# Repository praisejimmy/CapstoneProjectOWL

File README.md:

# CapstoneProjectOWL
CPE capstone repository for Project OWL

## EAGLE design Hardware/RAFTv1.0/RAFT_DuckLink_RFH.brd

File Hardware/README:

Capstone Project RAFT Hardware
***
Ryan Myers
Tristan Chutka
Jake Loveland
Noah Palumbo
***

This folder contains all hardware design files for the RAFT system.
Autodesk EAGLE is used for circuit and PCB design.

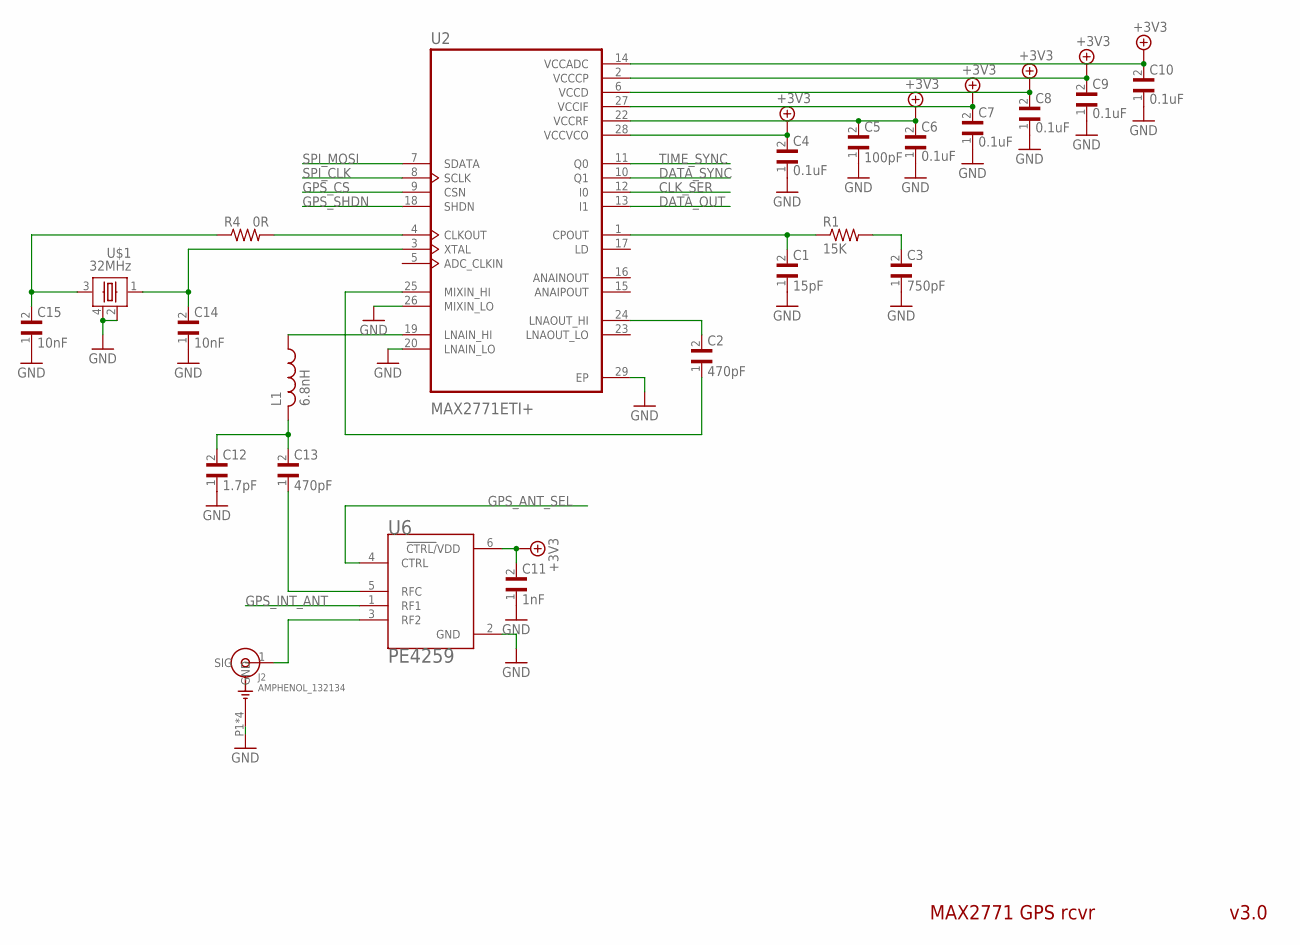
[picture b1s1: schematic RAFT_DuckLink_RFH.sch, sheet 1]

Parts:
C1: 15pF; CAPC1005X55N
C2, C13: 470pF; CAPC1005X55N
C3: 750pF; CAPC1608X90N
C4, C6, C7, C8, C9, C10: 0.1uF; CAPC1005X55N
C5: 100pF; CAPC1005X55N
C11: 1nF; CAPC1005X55N
C12: 1.7pF; CAPC1005X55N
C14, C15: 10nF; CAPC1005X55N
J2: AMPHENOL_132134; AMPHENOL_132134-15
L1: 6.8nH; INDC1005X55N
R1: 15K; RESC1005X40N
R4: 0R; RESC1005X40N
U2: MAX2771ETI+; QFN50P500X500X80-29N
U6: PE4259; SOT65P215X110-6N
U$1: 32MHz; SMD-4

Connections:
+3.3V: C4.2, C5.2, C6.2, C7.2, C8.2, C9.2, C10.2, C11.2, U2.2 (VCCCP), U2.6 (VCCD), U2.14 (VCCADC), U2.22 (VCCRF), U2.27 (VCCIF), U2.28 (VCCVCO), U6.6 (!CTRL/!VDD); also elsewhere on the board
CLK_SER: U2.12 (I0); also elsewhere on the board
DATA_OUT: U2.13 (I1); also elsewhere on the board
DATA_SYNC: U2.10 (Q1); also elsewhere on the board
GND: C1.1, C3.1, C4.1, C5.1, C6.1, C7.1, C8.1, C9.1, C10.1, C11.1, C12.1, C14.1, C15.1, J2.P1 (GND), J2.P2 (GND), J2.P3 (GND), J2.P4 (GND), U2.20 (LNAIN_LO), U2.26 (MIXIN_LO), U2.29 (EP), U6.2 (GND), U$1.2, U$1.4; also elsewhere on the board
GPS_ANT_SEL: U6.4 (CTRL); also elsewhere on the board
GPS_CS: U2.9 (CSN); also elsewhere on the board
GPS_INT_ANT: U6.1 (RF1); also elsewhere on the board
GPS_SHDN: U2.18 (SHDN); also elsewhere on the board
unnamed: C1.2, R1.1, U2.1 (CPOUT)
unnamed: C3.2, R1.2
unnamed: C2.2, U2.24 (LNAOUT_HI)
unnamed: C2.1, U2.25 (MIXIN_HI)
unnamed: L1.1, U2.19 (LNAIN_HI)
unnamed: C13.1, U6.5 (RFC)
unnamed: J2.1 (SIG), U6.3 (RF2)
unnamed: C12.2, C13.2, L1.2
unnamed: C15.2, R4.1, U$1.3
unnamed: C14.2, U2.3 (XTAL), U$1.1
unnamed: R4.2, U2.4 (CLKOUT)
SPI_CLK: U2.8 (SCLK); also elsewhere on the board
SPI_MOSI: U2.7 (SDATA); also elsewhere on the board
TIME_SYNC: U2.11 (Q0); also elsewhere on the board

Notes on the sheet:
MAX2771 GPS rcvr
v3.0

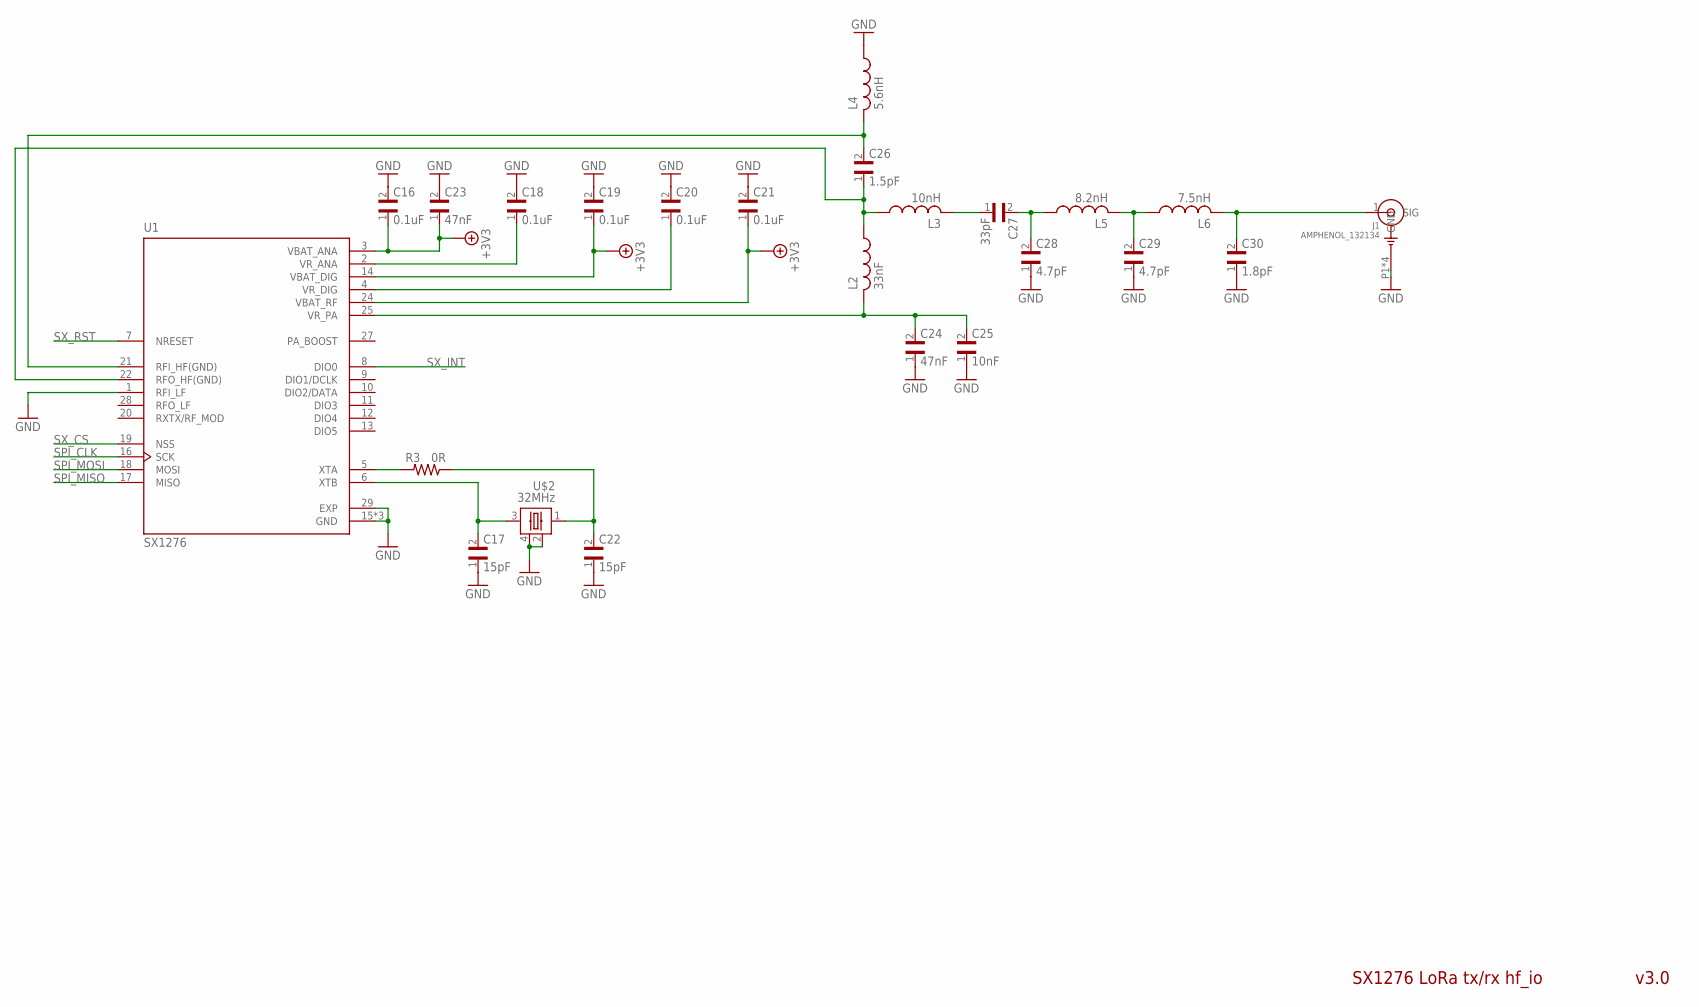
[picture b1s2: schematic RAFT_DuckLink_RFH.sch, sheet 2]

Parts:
C16, C18, C19, C20, C21: 0.1uF; CAPC1005X55N
C17, C22: 15pF; CAPC1005X55N
C23, C24: 47nF; CAPC1005X55N
C25: 10nF; CAPC1005X55N
C26: 1.5pF; CAPC1005X55N
C27: 33pF; CAPC1005X55N
C28, C29: 4.7pF; CAPC1005X55N
C30: 1.8pF; CAPC1005X55N
J1: AMPHENOL_132134; AMPHENOL_132134-15
L2: 33nF; INDC1005X55N
L3: 10nH; INDC1005X55N
L4: 5.6nH; INDC1005X55N
L5: 8.2nH; INDC1005X55N
L6: 7.5nH; INDC1005X55N
R3: 0R; RESC1005X40N
U1: SX1276; QFN65P600X600X100-29N
U$2: 32MHz; SMD-4

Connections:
+3.3V: C16.1, C19.1, C21.1, C23.1, U1.3 (VBAT_ANA), U1.14 (VBAT_DIG), U1.24 (VBAT_RF); also elsewhere on the board
GND: C16.2, C17.1, C18.2, C19.2, C20.2, C21.2, C22.1, C23.2, C24.1, C25.1, C28.1, C29.1, C30.1, J1.P1 (GND), J1.P2 (GND), J1.P3 (GND), J1.P4 (GND), L4.1, U1.1 (RFI_LF), U1.15 (GND), U1.23 (GND), U1.26 (GND), U1.29 (EXP), U$2.2, U$2.4; also elsewhere on the board
unnamed: C24.2, C25.2, L2.2, U1.25 (VR_PA)
unnamed: C18.1, U1.2 (VR_ANA)
unnamed: C22.2, R3.1, U$2.1
unnamed: C20.1, U1.4 (VR_DIG)
unnamed: C17.2, U1.6 (XTB), U$2.3
unnamed: C26.1, L2.1, L3.1, U1.22 (RFO_HF(GND))
unnamed: C26.2, L4.2, U1.21 (RFI_HF(GND))
unnamed: C27.1, L3.2
unnamed: C27.2, C28.2, L5.1
unnamed: C29.2, L5.2, L6.1
unnamed: C30.2, J1.1 (SIG), L6.2
unnamed: R3.2, U1.5 (XTA)
SPI_CLK: U1.16 (SCK); also elsewhere on the board
SPI_MISO: U1.17 (MISO); also elsewhere on the board
SPI_MOSI: U1.18 (MOSI); also elsewhere on the board
SX_CS: U1.19 (NSS); also elsewhere on the board
SX_INT: U1.8 (DIO0); also elsewhere on the board
SX_RST: U1.7 (NRESET); also elsewhere on the board

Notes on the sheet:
SX1276 LoRa tx/rx hf_io
v3.0

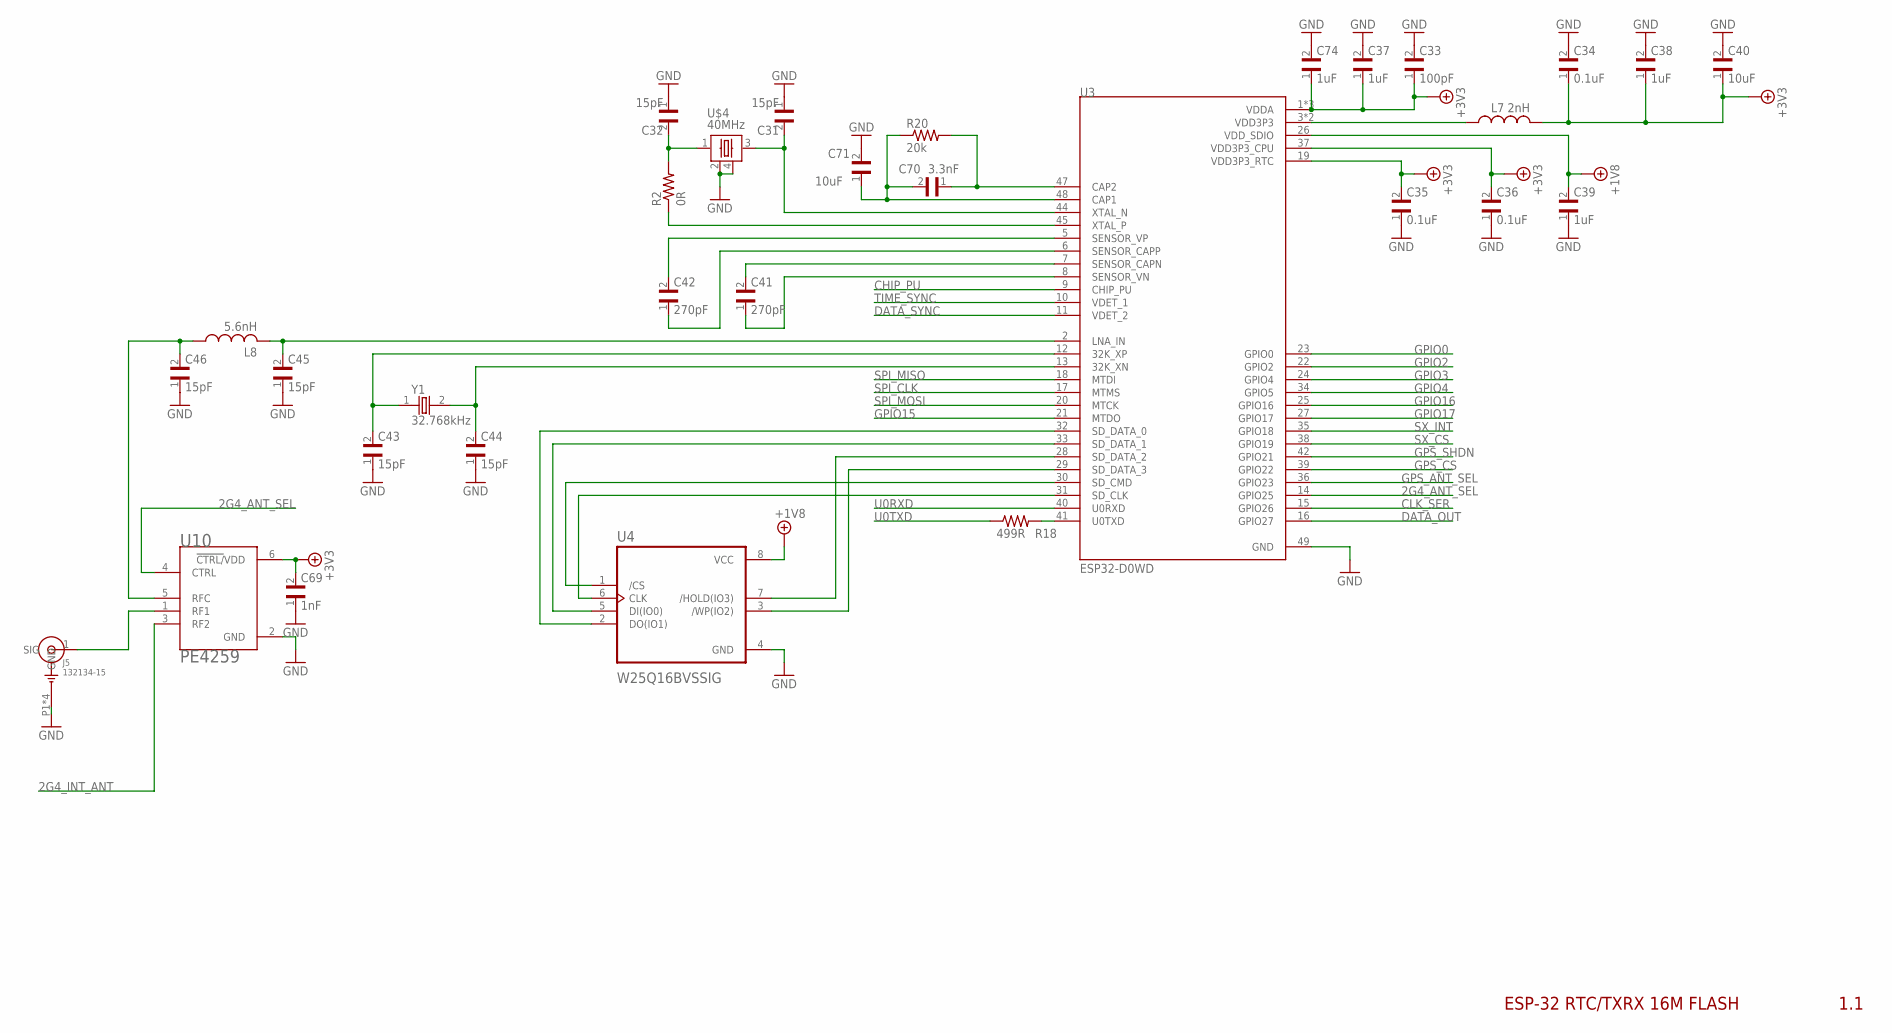
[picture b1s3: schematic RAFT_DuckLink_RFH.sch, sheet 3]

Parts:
C31, C32, C43, C44, C45, C46: 15pF; CAPC1005X55N
C33: 100pF; CAPC1005X55N
C34, C35, C36: 0.1uF; CAPC1005X55N
C37, C38, C39, C74: 1uF; CAPC1005X70N
C40, C71: 10uF; CAPC1005X70N
C41, C42: 270pF; CAPC1005X55N
C69: 1nF; CAPC1005X55N
C70: 3.3nF; CAPC1005X55N
J5: 132134-15; AMPHENOL_132134-15
L7: 2nH; INDC1005X55N
L8: 5.6nH; INDC1005X55N
R2: 0R; RESC1005X40N
R18: 499R; RESC1005X35N
R20: 20k; RESC1005X35N
U3: ESP32-D0WD; QFN35P500X500X90-49N
U4: W25Q16BVSSIG; SOIC127P790X216-8N
U10: PE4259; SOT65P215X110-6N
U$4: 40MHz; SMD-4
Y1: 32.768kHz; OSCCC150X320X80-2N

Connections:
2G4_ANT_SEL: U3.14 (GPIO25), U10.4 (CTRL)
2G4_INT_ANT: U10.3 (RF2); also elsewhere on the board
+1.8V: C39.2, U3.26 (VDD_SDIO), U4.8 (VCC)
+3.3V: C33.1, C34.1, C35.2, C36.2, C37.1, C38.1, C40.1, C69.2, C74.1, L7.2, U3.1 (VDDA), U3.19 (VDD3P3_RTC), U3.37 (VDD3P3_CPU), U3.43 (VDDA), U3.46 (VDDA), U10.6 (!CTRL/!VDD); also elsewhere on the board
CHIP_PU: U3.9 (CHIP_PU); also elsewhere on the board
CLK_SER: U3.15 (GPIO26); also elsewhere on the board
DATA_OUT: U3.16 (GPIO27); also elsewhere on the board
DATA_SYNC: U3.11 (VDET_2); also elsewhere on the board
GND: C31.1, C32.1, C33.2, C34.2, C35.1, C36.1, C37.2, C38.2, C39.1, C40.2, C43.1, C44.1, C45.1, C46.1, C69.1, C71.2, C74.2, J5.P1 (GND), J5.P2 (GND), J5.P3 (GND), J5.P4 (GND), U3.49 (GND), U4.4 (GND), U10.2 (GND), U$4.2, U$4.4; also elsewhere on the board
GPIO0: U3.23 (GPIO0); also elsewhere on the board
GPIO2: U3.22 (GPIO2); also elsewhere on the board
GPIO3: U3.24 (GPIO4); also elsewhere on the board
GPIO4: U3.34 (GPIO5); also elsewhere on the board
GPIO15: U3.21 (MTDO); also elsewhere on the board
GPIO16: U3.25 (GPIO16); also elsewhere on the board
GPIO17: U3.27 (GPIO17); also elsewhere on the board
GPS_ANT_SEL: U3.36 (GPIO23); also elsewhere on the board
GPS_CS: U3.39 (GPIO22); also elsewhere on the board
GPS_SHDN: U3.42 (GPIO21); also elsewhere on the board
unnamed: R2.1, U3.45 (XTAL_P)
unnamed: C31.2, U3.44 (XTAL_N), U$4.3
unnamed: L7.1, U3.3 (VDD3P3), U3.4 (VDD3P3)
unnamed: C41.1, U3.8 (SENSOR_VN)
unnamed: C41.2, U3.7 (SENSOR_CAPN)
unnamed: C42.1, U3.6 (SENSOR_CAPP)
unnamed: C42.2, U3.5 (SENSOR_VP)
unnamed: C32.2, R2.2, U$4.1
unnamed: R18.2, U3.41 (U0TXD)
unnamed: U3.30 (SD_CMD), U4.1 (/CS)
unnamed: U3.31 (SD_CLK), U4.6 (CLK)
unnamed: U3.28 (SD_DATA_2), U4.7 (/HOLD(IO3))
unnamed: U3.29 (SD_DATA_3), U4.3 (/WP(IO2))
unnamed: U3.33 (SD_DATA_1), U4.5 (DI(IO0))
unnamed: U3.32 (SD_DATA_0), U4.2 (DO(IO1))
unnamed: C43.2, U3.12 (32K_XP), Y1.1
unnamed: C46.2, L8.1, U10.5 (RFC)
unnamed: C44.2, U3.13 (32K_XN), Y1.2
unnamed: C45.2, L8.2, U3.2 (LNA_IN)
unnamed: J5.1 (SIG), U10.1 (RF1)
unnamed: C70.1, R20.2, U3.47 (CAP2)
unnamed: C70.2, C71.1, R20.1, U3.48 (CAP1)
SPI_CLK: U3.17 (MTMS); also elsewhere on the board
SPI_MISO: U3.18 (MTDI); also elsewhere on the board
SPI_MOSI: U3.20 (MTCK); also elsewhere on the board
SX_CS: U3.38 (GPIO19); also elsewhere on the board
SX_INT: U3.35 (GPIO18); also elsewhere on the board
TIME_SYNC: U3.10 (VDET_1); also elsewhere on the board
U0RXD: U3.40 (U0RXD); also elsewhere on the board
U0TXD: R18.1; also elsewhere on the board

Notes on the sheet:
1.1
ESP-32 RTC/TXRX 16M FLASH

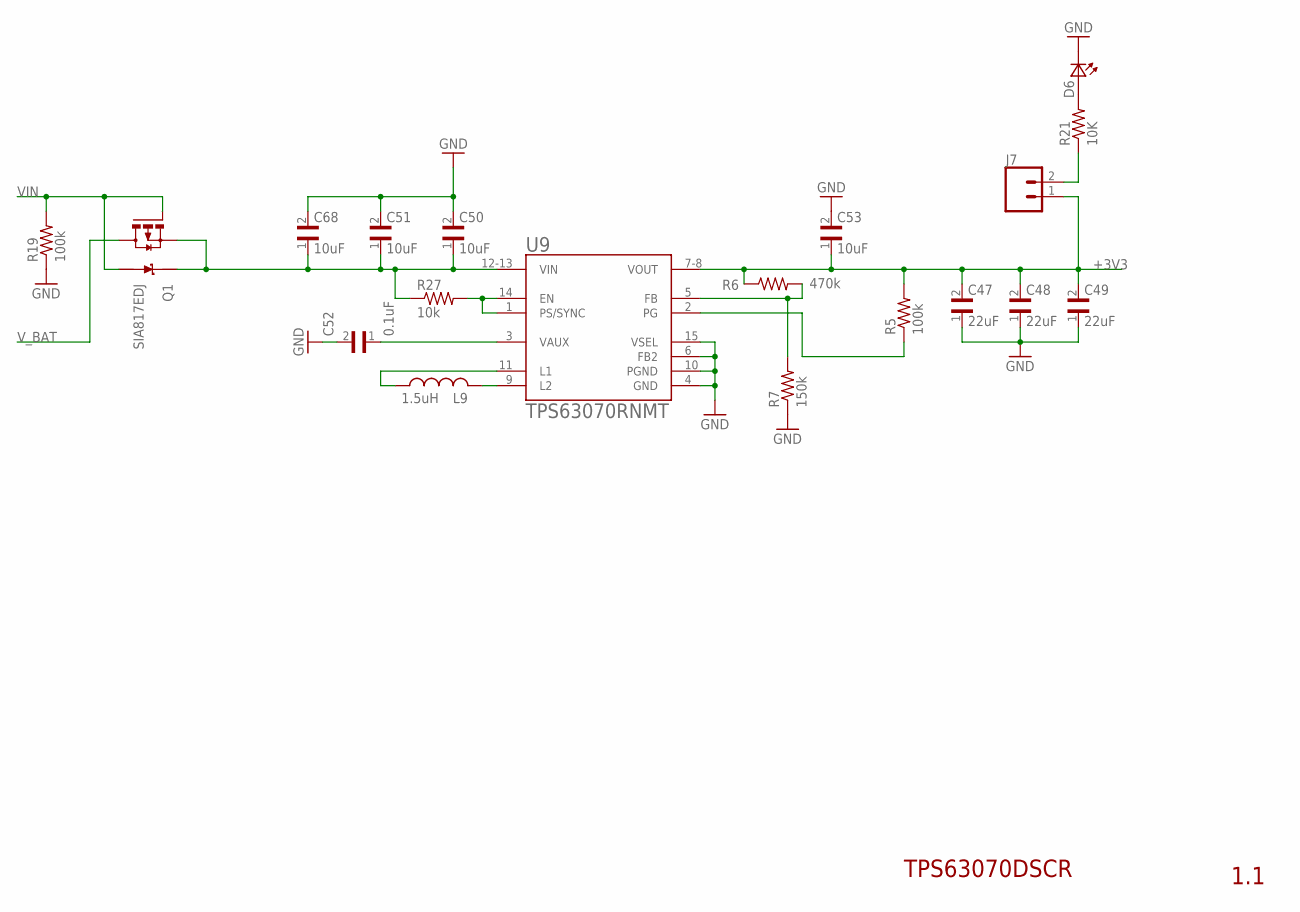
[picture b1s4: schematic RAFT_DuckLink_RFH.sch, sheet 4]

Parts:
C47, C48, C49: 22uF; CAPC1608X100N
C50, C51, C53, C68: 10uF; CAPC1005X70N
C52: 0.1uF; CAPC1005X55N
D6: LTST-C190GKT; 0603
J7: CONN_02; 1X02
L9: 1.5uH; INDC1608X95N
Q1: SIA817EDJ; POWERPAKSC-70
R5, R19: 100k; RESC1005X40N
R6: 470k; RESC1005X35N
R7: 150k; RESC1005X35N
R21: 10K; RESC1005X40N
R27: 10k; RESC1005X40N
U9: TPS63070RNMT; QFN50P250X300X100-15N

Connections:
+3V3: C47.2, C48.2, C49.2, C53.1, J7.1, R5.2, R6.1, U9.7-8 (VOUT)
GND: C47.1, C48.1, C49.1, C50.2, C51.2, C52.2, C53.2, C68.2, D6.1 (K2), R7.1, R19.1, U9.4 (GND), U9.6 (FB2), U9.10 (PGND), U9.15 (VSEL); also elsewhere on the board
unnamed: C52.1, U9.3 (VAUX)
unnamed: L9.1, U9.11 (L1)
unnamed: L9.2, U9.9 (L2)
unnamed: R5.1, U9.2 (PG)
unnamed: R6.2, R7.2, U9.5 (FB)
unnamed: D6.2 (A2), R21.2
unnamed: R27.2, U9.1 (PS/SYNC), U9.14 (EN)
unnamed: J7.2, R21.1
VIN: Q1.1 (A), Q1.5 (G), R19.2; also elsewhere on the board
VIN_SYS: C50.1, C51.1, C68.1, Q1.4 (S), Q1.6 (K), R27.1, U9.12-13 (VIN)
V_BAT: Q1.3 (D); also elsewhere on the board

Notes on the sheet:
TPS63070DSCR
1.1

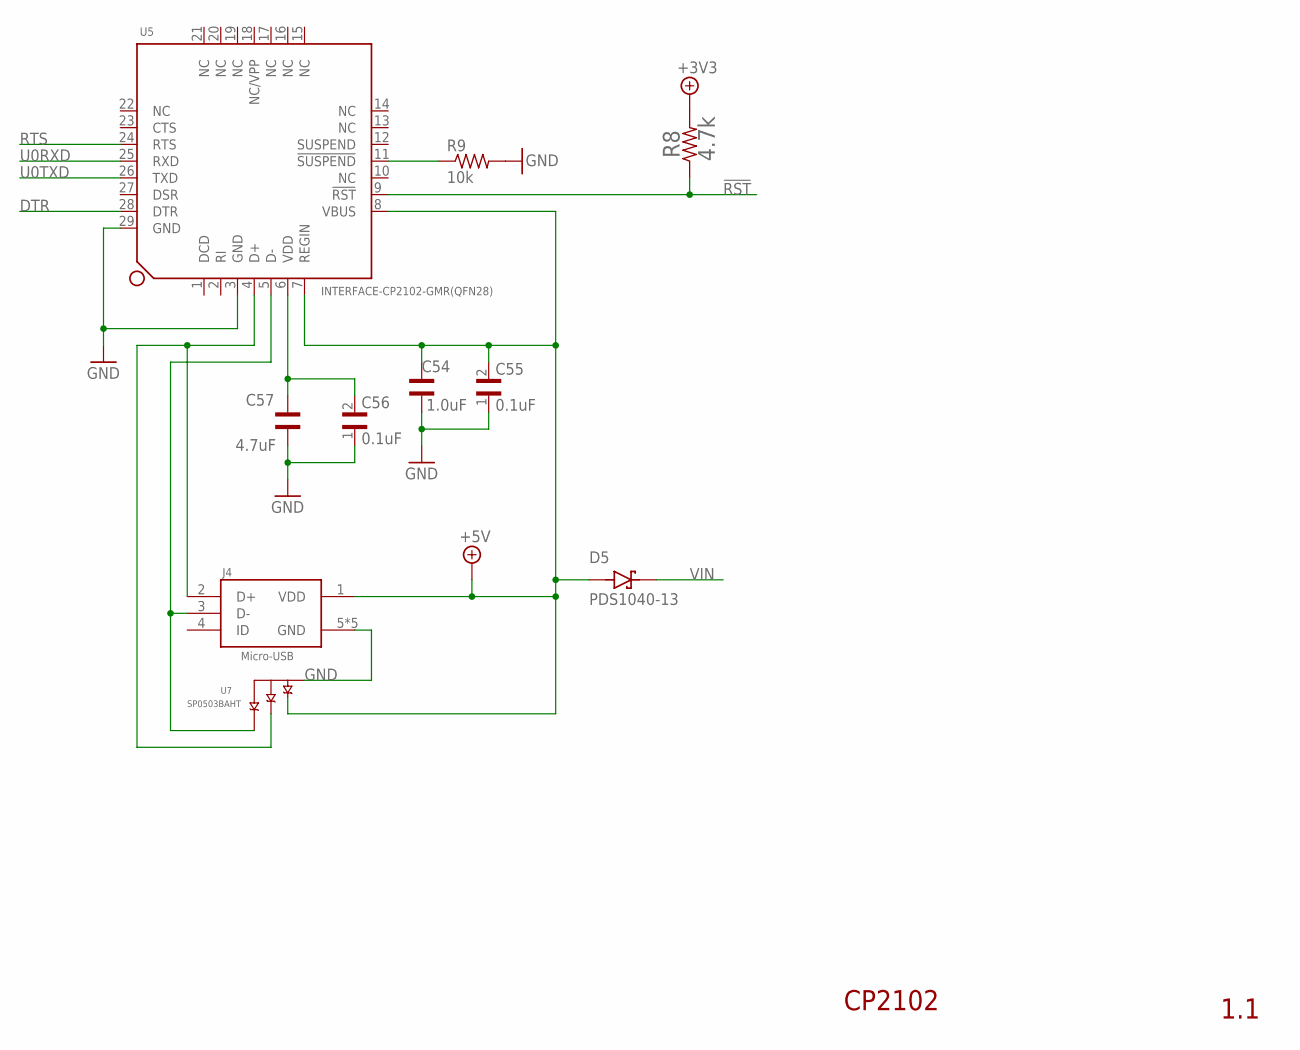
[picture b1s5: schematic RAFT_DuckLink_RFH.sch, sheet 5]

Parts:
C54: 1.0uF; CAPC1005X70N
C55, C56: 0.1uF; CAPC1005X55N
C57: 4.7uF; CAPC1005X55N
D5: PDS1040-13; DIO_PDS1040-13
J4: Micro-USB; MOLEX_105017-0001
R8: 4.7k; RESC1005X35N
R9: 10k; RESC1005X40N
U5: INTERFACE-CP2102-GMR(QFN28); QFN28G_0.5-5X5MM
U7: SP0503BAHT; SOT143

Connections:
!RST: R8.1, U5.9 (!RST)
+3.3V: R8.2; also elsewhere on the board
+5V: C54.2, C55.2, D5.1 (A), D5.2 (A), J4.1 (VDD), U5.7 (REGIN), U5.8 (VBUS), U7.2 (A); also elsewhere on the board
DTR: U5.28 (DTR); also elsewhere on the board
GND: C54.1, C55.1, C56.1, C57.1, J4.5 (GND), J4.P$1 (GND), J4.P$2 (GND), J4.P$8 (GND), J4.P$9 (GND), R9.2, U5.3 (GND), U5.29 (GND), U7.1 (GND); also elsewhere on the board
unnamed: R9.1, U5.11 (!SUSPEND)
unnamed: C56.2, C57.2, U5.6 (VDD)
unnamed: J4.3 (D-), U5.5 (D-), U7.4 (C)
unnamed: J4.2 (D+), U5.4 (D+), U7.3 (B)
RTS: U5.24 (RTS); also elsewhere on the board
U0RXD: U5.25 (RXD); also elsewhere on the board
U0TXD: U5.26 (TXD); also elsewhere on the board
VIN: D5.3 (K); also elsewhere on the board

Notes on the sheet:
CP2102
1.1

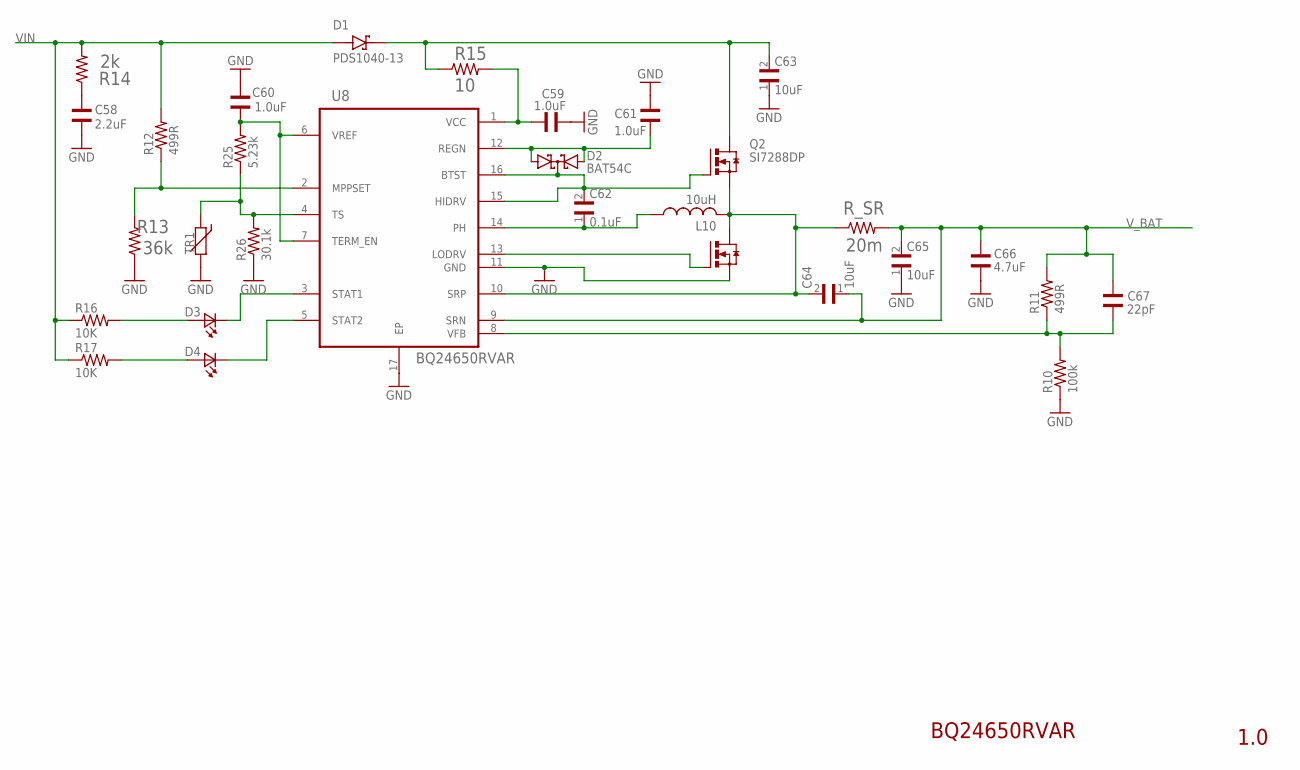
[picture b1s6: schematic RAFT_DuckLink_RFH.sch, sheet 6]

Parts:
C58: 2.2uF; CAPC1005X55N
C59, C60, C61: 1.0uF; CAPC1005X70N
C62: 0.1uF; CAPC1005X55N
C63, C64, C65: 10uF; CAPC1005X70N
C66: 4.7uF; CAPC1005X55N
C67: 22pF; CAPC1005X55N
D1: PDS1040-13; DIO_PDS1040-13
D2: BAT54C; SOT23
D3, D4: LTST-C190GKT; 0603
L10: 10uH; INDC1608X90N
Q2: SI7288DP; POWERPAK-SO8_1
R10: 100k; RESC1005X40N
R11, R12: 499R; RESC1005X35N
R13: 36k; RESC1005X40N
R14: 2k; RESC1005X40N
R15: 10; RESC1005X35N
R16, R17: 10K; RESC1005X40N
R25: 5.23k; RESC1005X40N
R26: 30.1k; RESC1005X40N
R_SR: 20m; RESC1608X55N
TR1: THERMISTOR_R-2,5; RS-2,5
U8: BQ24650RVAR; QFN50P350X350X100-17N

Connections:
GND: C58.1, C59.2, C60.2, C61.2, C63.1, C65.1, C66.1, Q2.3 (S1), R10.1, R13.1, R26.1, TR1.2, U8.11 (GND), U8.17 (EP); also elsewhere on the board
unnamed: Q2.4 (G1), U8.13 (LODRV)
unnamed: C60.1, R25.2, U8.6 (VREF), U8.7 (TERM_EN)
unnamed: R12.1, R13.2, U8.2 (MPPSET)
unnamed: C59.1, R15.2, U8.1 (VCC)
unnamed: C61.1, D2.1 (A1), D2.2 (A2), U8.12 (REGN)
unnamed: C62.2, D2.3 (CC), Q2.2 (G), U8.15 (HIDRV), U8.16 (BTST)
unnamed: C67.1, R10.2, R11.1, U8.8 (VFB)
unnamed: C64.2, L10.2, Q2.1 (S), Q2.5 (D1), Q2.6 (D1), R_SR.1, U8.10 (SRP)
unnamed: D4.2 (A2), R17.2
unnamed: D3.2 (A2), R16.2
unnamed: D4.1 (K2), U8.5 (STAT2)
unnamed: D3.1 (K2), U8.3 (STAT1)
unnamed: C62.1, L10.1, U8.14 (PH)
unnamed: C58.2, R14.1
PACK_THERM: R25.1, R26.2, TR1.1, U8.4 (TS)
SC_VIN: C63.2, D1.3 (K), Q2.7 (D), Q2.8 (D), R15.1
VIN: D1.1 (A), D1.2 (A), R12.2, R14.2, R16.1, R17.1; also elsewhere on the board
V_BAT: C64.1, C65.2, C66.2, C67.2, R11.2, R_SR.2, U8.9 (SRN); also elsewhere on the board

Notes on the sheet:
BQ24650RVAR
1.0

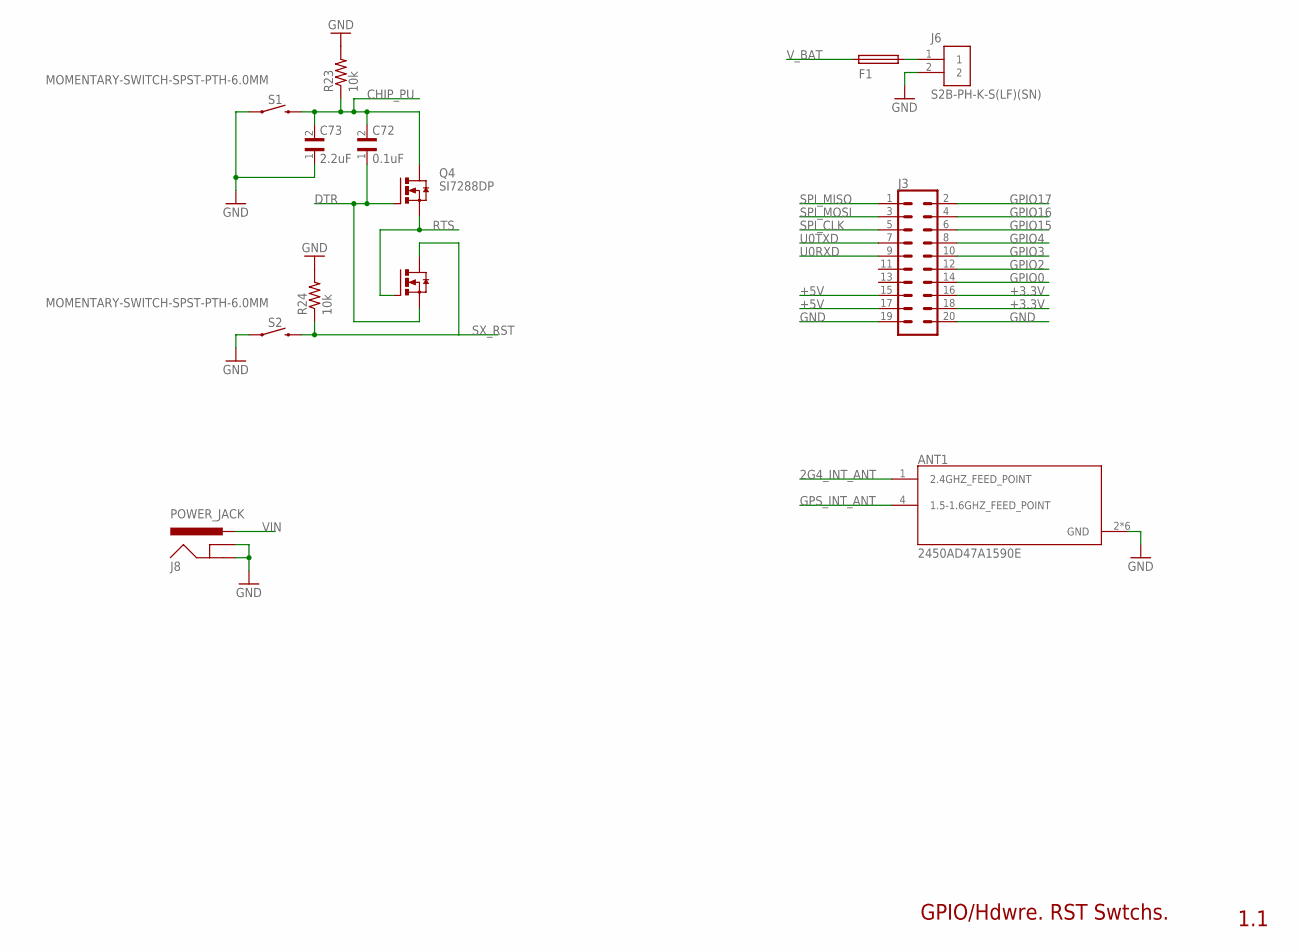
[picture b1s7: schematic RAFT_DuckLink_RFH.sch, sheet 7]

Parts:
ANT1: 2450AD47A1590E; ANT_2450AD47A1590E
C72: 0.1uF; CAPC1005X55N
C73: 2.2uF; CAPC1005X55N
F1: LITTLEFUSE
J3: CONN_10X2; 2X10
J6: S2B-PH-K-S(LF)(SN); JST_S2B-PH-K-S(LF)(SN)
J8: POWER_JACK; POWER_JACK_PTH
Q4: SI7288DP; POWERPAK-SO8_1
R23, R24: 10k; RESC1005X40N
S1, S2: MOMENTARY-SWITCH-SPST-PTH-6.0MM; TACTILE_SWITCH_PTH_6.0MM

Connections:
2G4_INT_ANT: ANT1.1 (2.4GHZ_FEED_POINT); also elsewhere on the board
+3.3V: J3.16, J3.18; also elsewhere on the board
+5V: J3.15, J3.17; also elsewhere on the board
CHIP_PU: C72.2, C73.2, Q4.7 (D), Q4.8 (D), R23.1, S1.3 (2); also elsewhere on the board
DTR: C72.1, Q4.2 (G), Q4.3 (S1); also elsewhere on the board
GND: ANT1.2 (GND), ANT1.3 (GND), ANT1.5 (GND), ANT1.6 (GND), ANT1.7 (GND), ANT1.8 (GND), C73.1, J3.19, J3.20, J6.2, J8.GND, J8.GNDBREAK, R23.2, R24.2, S1.1, S2.1; also elsewhere on the board
GPIO0: J3.14; also elsewhere on the board
GPIO2: J3.12; also elsewhere on the board
GPIO3: J3.10; also elsewhere on the board
GPIO4: J3.8; also elsewhere on the board
GPIO15: J3.6; also elsewhere on the board
GPIO16: J3.4; also elsewhere on the board
GPIO17: J3.2; also elsewhere on the board
GPS_INT_ANT: ANT1.4 (1.5-1.6GHZ_FEED_POINT); also elsewhere on the board
unnamed: F1.2, J6.1
RTS: Q4.1 (S), Q4.4 (G1); also elsewhere on the board
SPI_CLK: J3.5; also elsewhere on the board
SPI_MISO: J3.1; also elsewhere on the board
SPI_MOSI: J3.3; also elsewhere on the board
SX_RST: Q4.5 (D1), Q4.6 (D1), R24.1, S2.3 (2); also elsewhere on the board
U0RXD: J3.9; also elsewhere on the board
U0TXD: J3.7; also elsewhere on the board
VIN: J8.PWR; also elsewhere on the board
V_BAT: F1.1; also elsewhere on the board

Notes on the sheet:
GPIO/Hdwre. RST Swtchs.
1.1

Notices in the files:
parts and their libraries:
SparkFun-Connectors: Licensing: Creative Commons ShareAlike 4.0 International - https://creativecommons.org/licenses/by-sa/4.0
COPYRIGHT: Copyright (C) 2015 Accelerated Designs. All rights reserved
COPYRIGHT: Copyright (C) 2018 Accelerated Designs. All rights reserved
